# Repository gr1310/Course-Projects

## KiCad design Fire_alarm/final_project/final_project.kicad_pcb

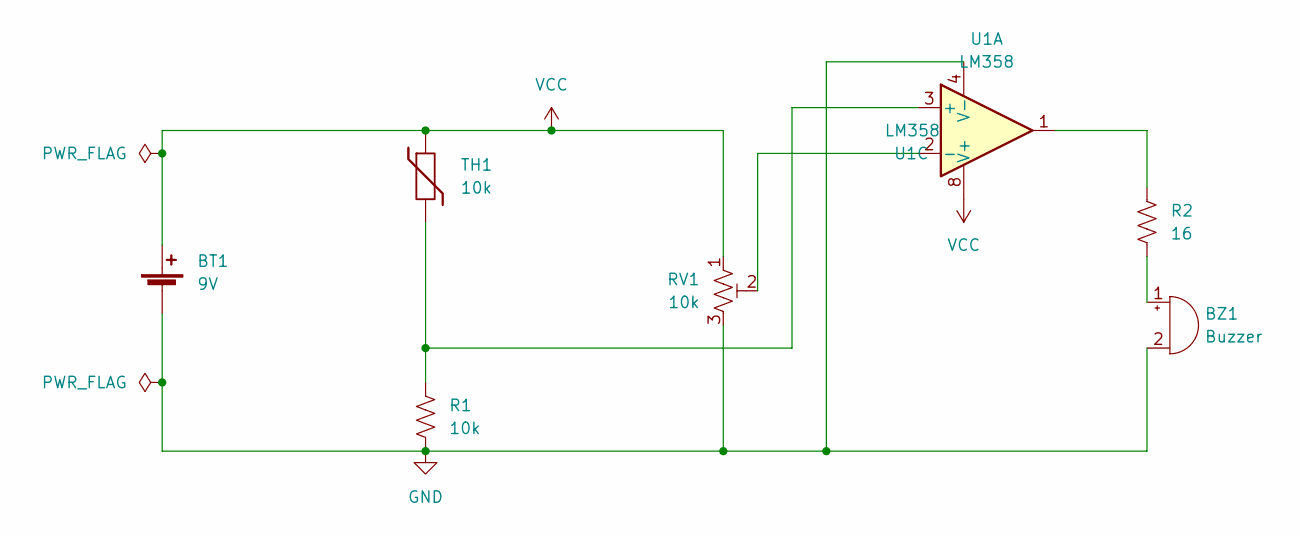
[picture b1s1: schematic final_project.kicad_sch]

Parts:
BT1: 9V; TerminalBlock_MetzConnect_Type101_RT01602HBWC_1x02_P5.08mm_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
BZ1: Buzzer; Buzzer_12x9.5RM7.6
R1: 10k; R_Axial_DIN0207_L6.3mm_D2.5mm_P10.16mm_Horizontal
R2: 16; R_Axial_DIN0207_L6.3mm_D2.5mm_P10.16mm_Horizontal
RV1: 10k; Potentiometer_Bourns_3296P_Horizontal
TH1: 10k; R_Axial_DIN0411_L9.9mm_D3.6mm_P12.70mm_Horizontal
U1: LM358; DIP-8_W10.16mm

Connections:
GND: BT1.2 (-), BZ1.2 (+), R1.2, RV1.3, U1.4 (V-)
unnamed: BZ1.1 (-), R2.2
unnamed: R1.1, TH1.2, U1.3 (+)
unnamed: R2.1, U1.1
unnamed: RV1.2, U1.2 (-)
VCC: BT1.1 (+), RV1.1, TH1.1, U1.8 (V+)

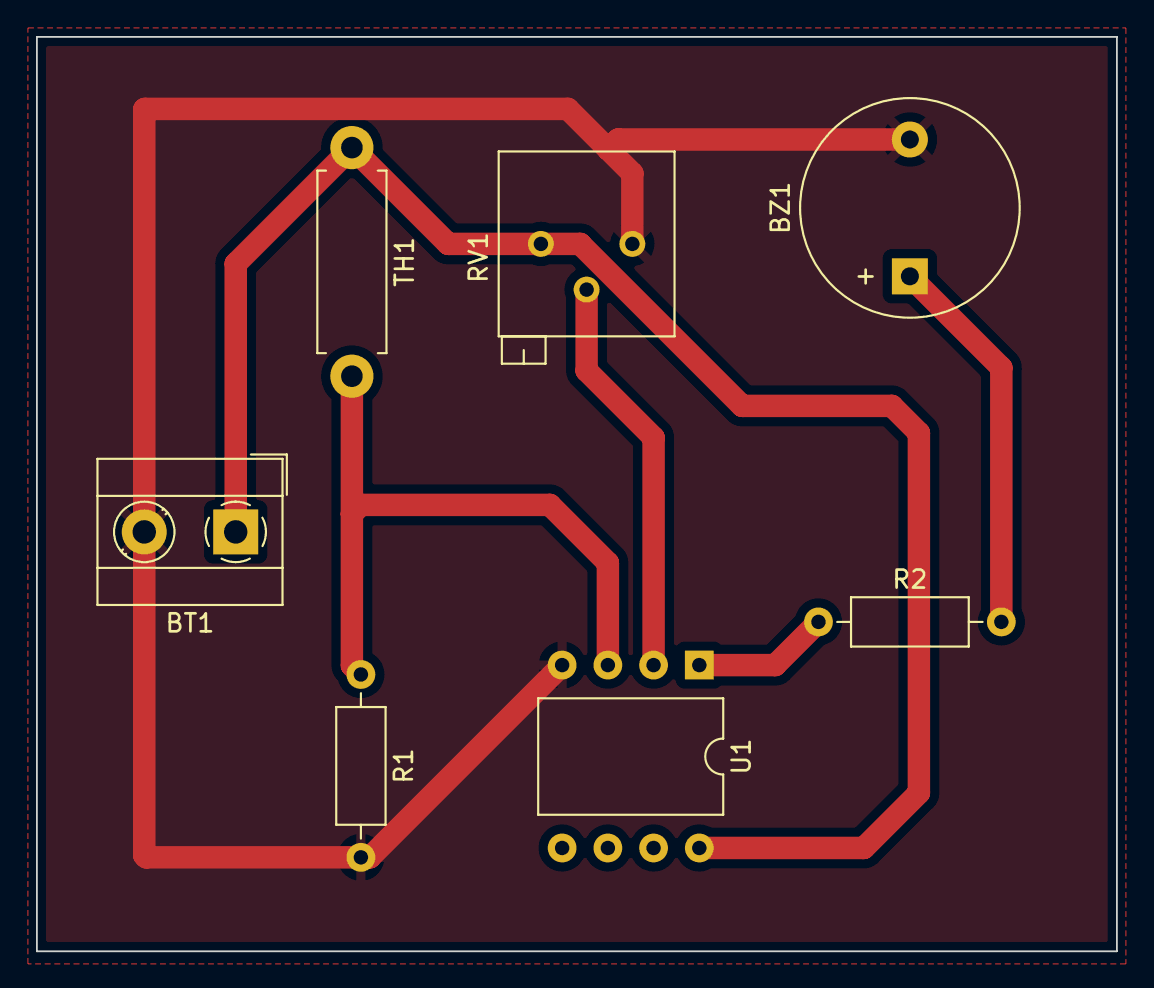
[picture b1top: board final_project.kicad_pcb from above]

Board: 2 copper layers, 60.0 x 50.8 mm, 7 parts (0 on the bottom side), 6 nets.

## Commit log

2023-07-18 Create More ML projects
